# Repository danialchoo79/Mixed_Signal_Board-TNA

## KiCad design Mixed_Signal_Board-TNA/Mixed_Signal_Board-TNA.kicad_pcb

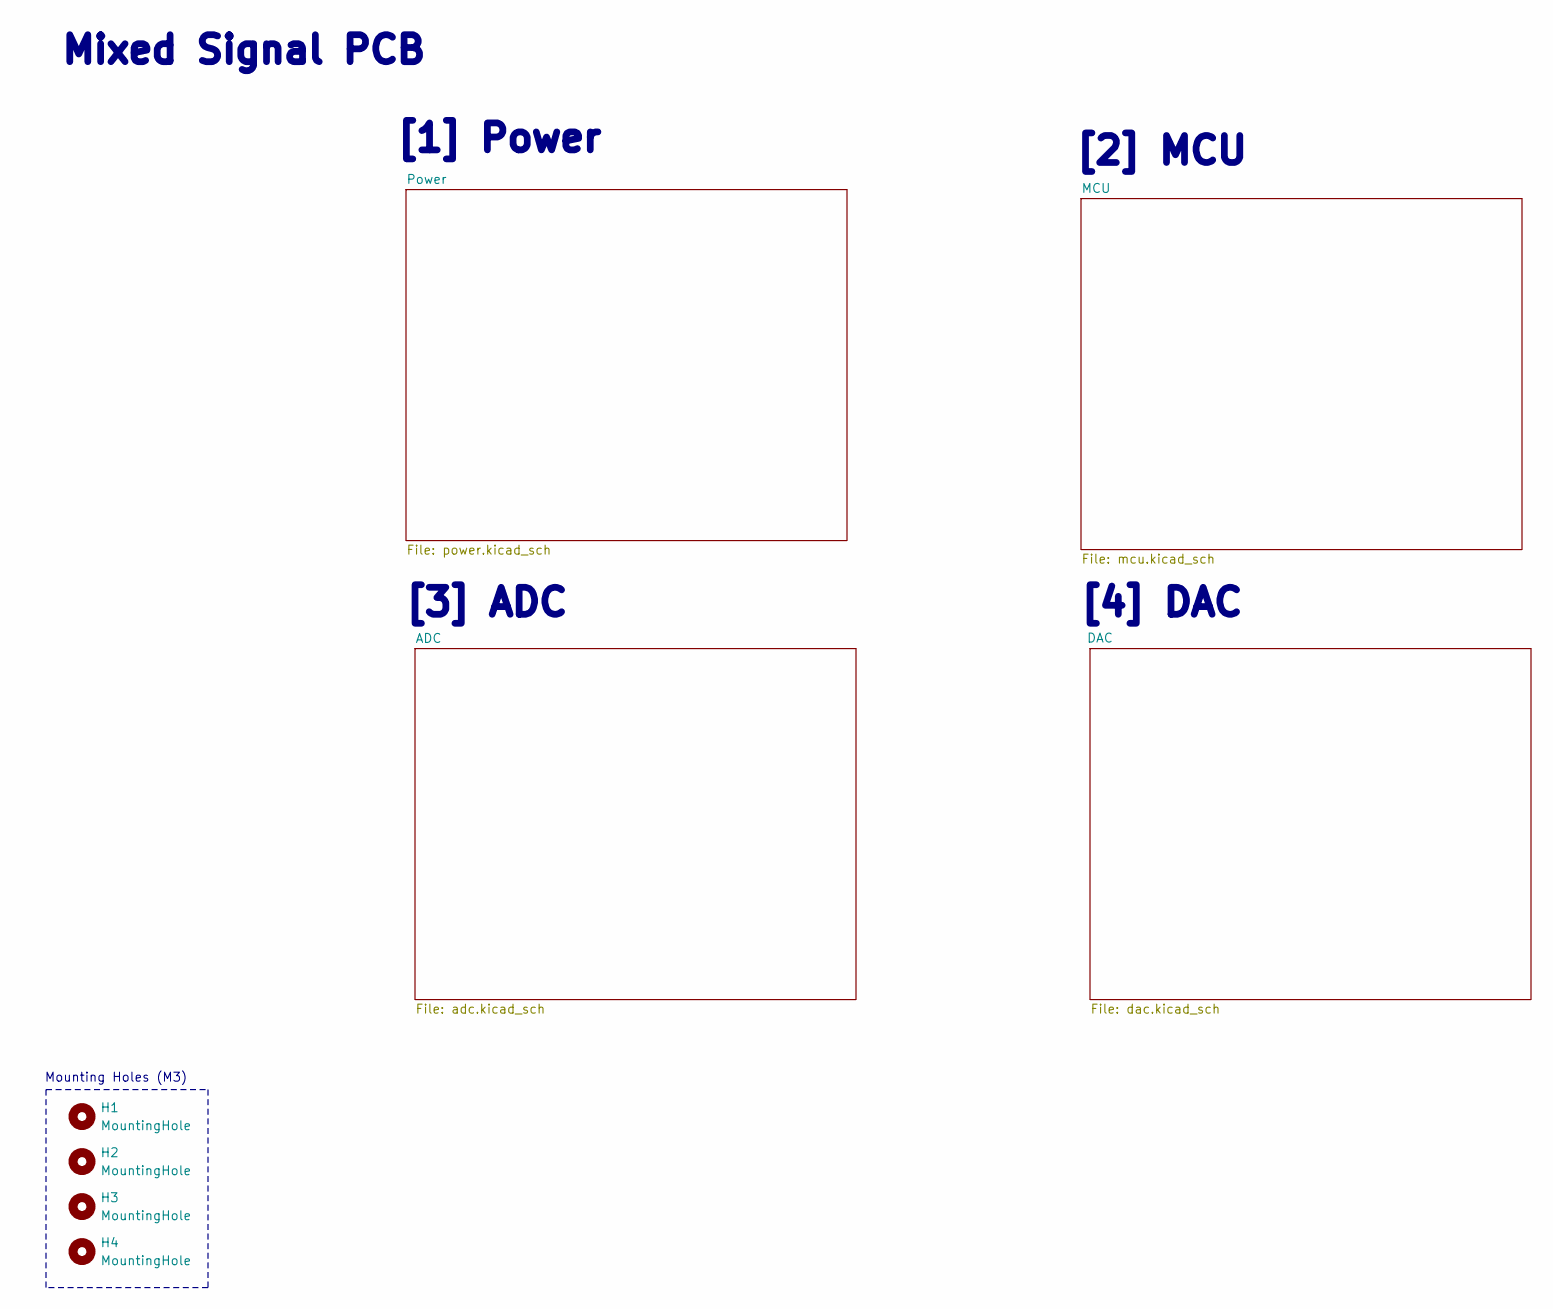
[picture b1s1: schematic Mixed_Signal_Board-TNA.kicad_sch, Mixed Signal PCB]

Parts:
H1, H2, H3, H4: MountingHole; MountingHole_3.2mm_M3

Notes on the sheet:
[2] MCU
[4] DAC
Mounting Holes (M3)
[3] ADC
Mixed Signal PCB
[1] Power

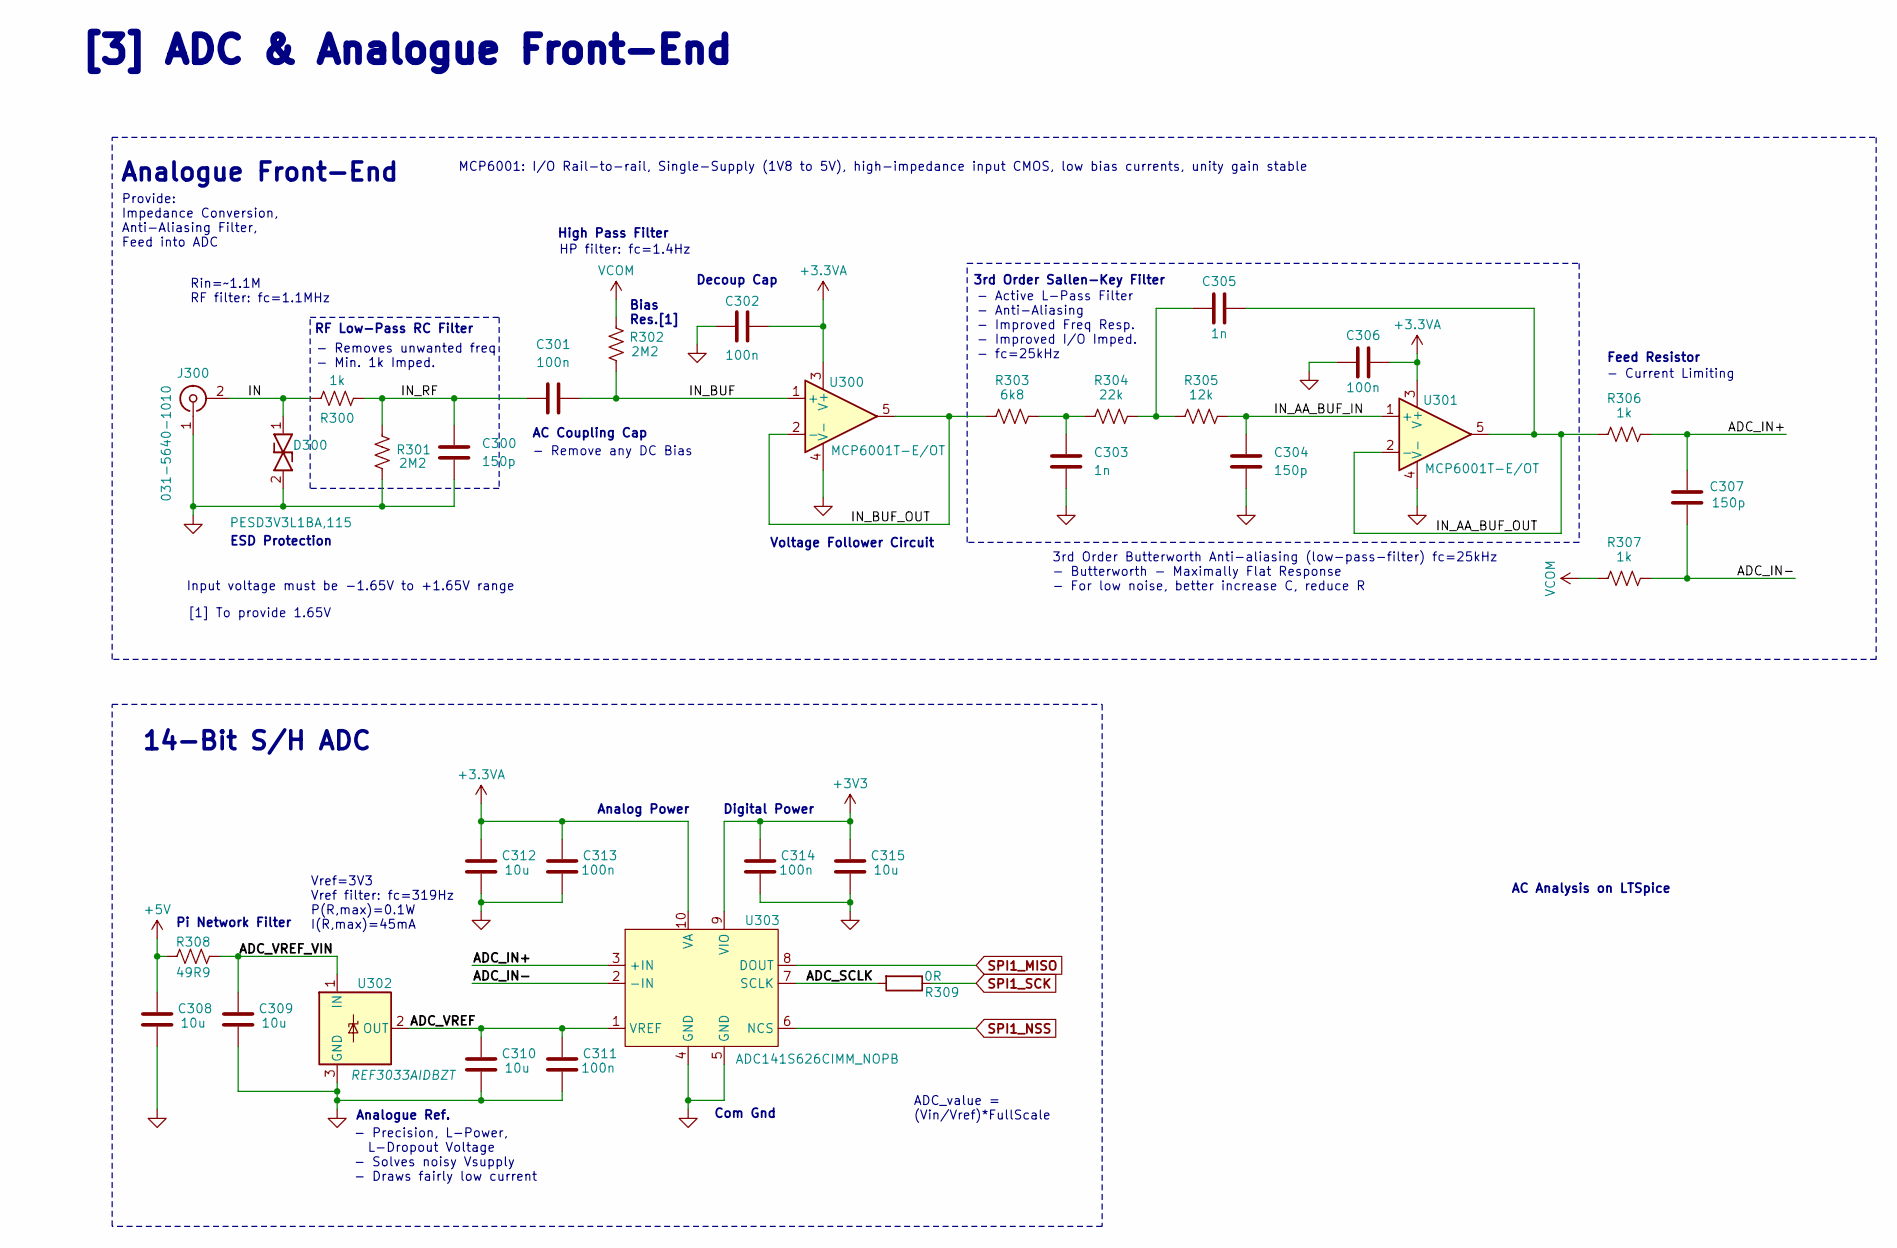
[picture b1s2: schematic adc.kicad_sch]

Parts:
C300, C304, C307: 150p; C_0402_1005Metric
C301, C302, C306, C311, C313, C314: 100n; C_0402_1005Metric
C303, C305: 1n; C_0402_1005Metric
C308, C309: 10u; C_0402_1005Metric
C310, C312, C315: 10u; C_0603_1608Metric
D300: PESD3V3L1BA,115; SOD2512X110N; Mouser Part Number 771-PESD3V3L1BA-T/R
J300: 031-5640-1010; 03156401010
R300, R306, R307: 1k; R_0402_1005Metric
R301, R302: 2M2; R_0603_1608Metric
R303: 6k8; R_0402_1005Metric
R304: 22k; R_0402_1005Metric
R305: 12k; R_0402_1005Metric
R308: 49R9; R_0402_1005Metric
R309: 0R; R_0402_1005Metric
U300, U301: MCP6001T-E/OT; SOT95P270X145-5N
U302: REF3033AIDBZT; SOT-23
U303: ADC141S626CIMM_NOPB; SOP50P490X110-10N

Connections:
+3.3VA: C302.1, C306.2, C312.1, C313.1, U300.3 (V+), U301.3 (V+), U303.10 (VA); also elsewhere on the board
+5V: C308.1, R308.2; also elsewhere on the board
/ADC/ADC_IN+: C307.1, R306.1, U303.3 (+IN)
/ADC/ADC_IN-: C307.2, R307.1, U303.2 (-IN)
/ADC/ADC_SCLK: R309.2, U303.7 (SCLK)
/ADC/ADC_VREF: C310.1, C311.1, U302.2 (OUT), U303.1 (VREF)
/ADC/ADC_VREF_VIN: C309.1, R308.1, U302.1 (IN)
/ADC/IN: D300.1 (K1), J300.2 (Ext), R300.2
/ADC/IN_AA_BUF_IN: C304.1, R305.1, U301.1 (+)
/ADC/IN_AA_BUF_OUT: C305.2, R306.2, U301.2 (-), U301.5
/ADC/IN_BUF: C301.1, R302.1, U300.1 (+)
/ADC/IN_BUF_OUT: R303.2, U300.2 (-), U300.5
/ADC/IN_RF: C300.1, C301.2, R300.1, R301.2
unnamed: C303.1, R303.1, R304.2
unnamed: C305.1, R304.1, R305.2
SPI1_MISO: U303.8 (DOUT); also elsewhere on the board
SPI1_NSS: U303.6 (NCS); also elsewhere on the board
SPI1_SCK: R309.1; also elsewhere on the board
VCOM: R302.2, R307.2; also elsewhere on the board
VREF_DAC: C300.2, C302.2, C303.2, C304.2, C306.1, C308.2, C309.2, C310.2, C311.2, C312.2, C313.2, C314.2, C315.2, D300.2 (K2), J300.1 (In), R301.1, U300.4 (V-), U301.4 (V-), U302.3 (GND), U303.4 (GND), U303.5 (GND); also elsewhere on the board

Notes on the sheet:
3rd Order Sallen-Key Filter
Decoup Cap
- Precision, L-Power, L-Dropout Voltage - Solves noisy Vsupply - Draws fairly low current
MCP6001: I/O Rail-to-rail, Single-Supply (1V8 to 5V), high-impedance input CMOS, low bias currents, unity gain stable
Pi Network Filter
ADC_value = (Vin/Vref)*FullScale
Voltage Follower Circuit
- Active L-Pass Filter - Anti-Aliasing - Improved Freq Resp. - Improved I/O Imped. - fc=25kHz
Analogue Ref.
RF Low-Pass RC Filter
[3] ADC & Analogue Front-End
HP filter: fc=1.4Hz
Feed Resistor
Com Gnd
High Pass Filter
Digital Power
Analogue Front-End
Analog Power
Bias Res.[1]
AC Coupling Cap
14-Bit S/H ADC
3rd Order Butterworth Anti-aliasing (low-pass-filter) fc=25kHz - Butterworth - Maximally Flat Response - For low noise, better increase C, reduce R
Provide: Impedance Conversion, Anti-Aliasing Filter, Feed into ADC
ESD Protection
AC Analysis on LTSpice
- Current Limiting
Input voltage must be -1.65V to +1.65V range
Rin=~1.1M RF filter: fc=1.1MHz
- Remove any DC Bias
Vref=3V3 Vref filter: fc=319Hz P(R,max)=0.1W I(R,max)=45mA
- Removes unwanted freq - Min. 1k Imped.
[1] To provide 1.65V

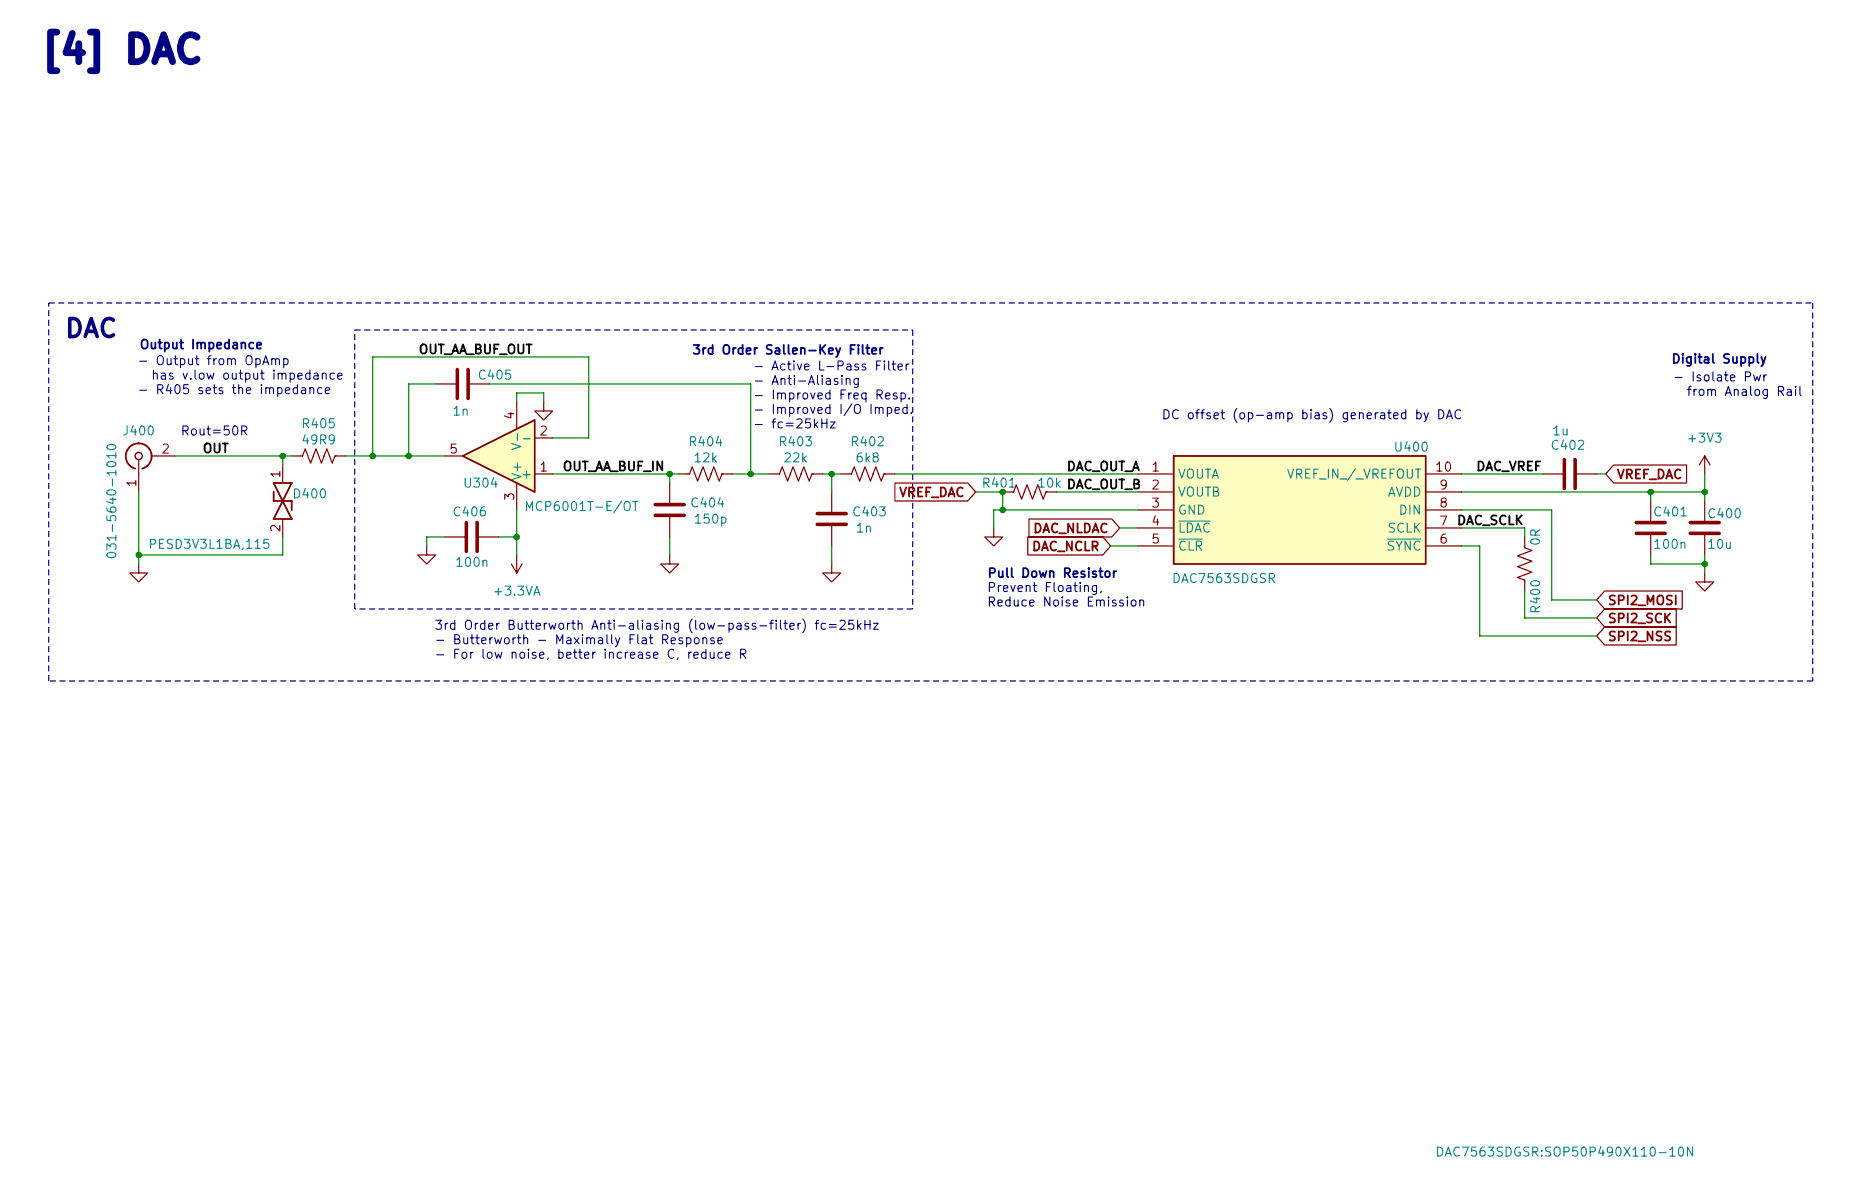
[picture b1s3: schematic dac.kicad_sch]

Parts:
C400: 10u; C_0603_1608Metric
C401, C406: 100n; C_0402_1005Metric
C402: 1u; C_0402_1005Metric
C403, C405: 1n; C_0402_1005Metric
C404: 150p; C_0402_1005Metric
D400: PESD3V3L1BA,115; SOD2512X110N; Mouser Part Number 771-PESD3V3L1BA-T/R
J400: 031-5640-1010; 03156401010
R400: 0R; R_0402_1005Metric
R401: 10k; R_0402_1005Metric
R402: 6k8; R_0402_1005Metric
R403: 22k; R_0402_1005Metric
R404: 12k; R_0402_1005Metric
R405: 49R9; R_0402_1005Metric
U304: MCP6001T-E/OT; SOT95P270X145-5N
U400: DAC7563SDGSR; SOP50P490X110-10N; Mouser Part Number 595-DAC7563SDGSR

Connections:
+3.3VA: C406.2, U304.3 (V+); also elsewhere on the board
/DAC/DAC_OUT_A: R402.1, U400.1 (VOUTA)
/DAC/DAC_OUT_B: R401.2, U400.2 (VOUTB)
/DAC/DAC_SCLK: R400.2, U400.7 (SCLK)
/DAC/DAC_VREF: C402.2, U400.10 (VREF_IN_/_VREFOUT)
/DAC/OUT: D400.1 (K1), J400.2 (Ext), R405.2
/DAC/OUT_AA_BUF_IN: C404.1, R404.2, U304.1 (+)
/DAC/OUT_AA_BUF_OUT: C405.1, R405.1, U304.2 (-), U304.5
DAC_NCLR: U400.5 (~CLR); also elsewhere on the board
DAC_NLDAC: U400.4 (~LDAC); also elsewhere on the board
unnamed: C403.1, R402.2, R403.1
unnamed: C405.2, R403.2, R404.1
SPI2_MOSI: U400.8 (DIN); also elsewhere on the board
SPI2_NSS: U400.6 (~SYNC); also elsewhere on the board
SPI2_SCK: R400.1; also elsewhere on the board
VREF_DAC: C400.2, C401.2, C402.1, C403.2, C404.2, C406.1, D400.2 (K2), J400.1 (In), R401.1, U304.4 (V-), U400.3 (GND); also elsewhere on the board

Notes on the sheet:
Rout=50R
[4] DAC
- Active L-Pass Filter - Anti-Aliasing - Improved Freq Resp. - Improved I/O Imped. - fc=25kHz
DAC
3rd Order Butterworth Anti-aliasing (low-pass-filter) fc=25kHz - Butterworth - Maximally Flat Response - For low noise, better increase C, reduce R
Pull Down Resistor
Output Impedance
Digital Supply
3rd Order Sallen-Key Filter
DC offset (op-amp bias) generated by DAC
Prevent Floating, Reduce Noise Emission
- Output from OpAmp has v.low output impedance - R405 sets the impedance
- Isolate Pwr from Analog Rail

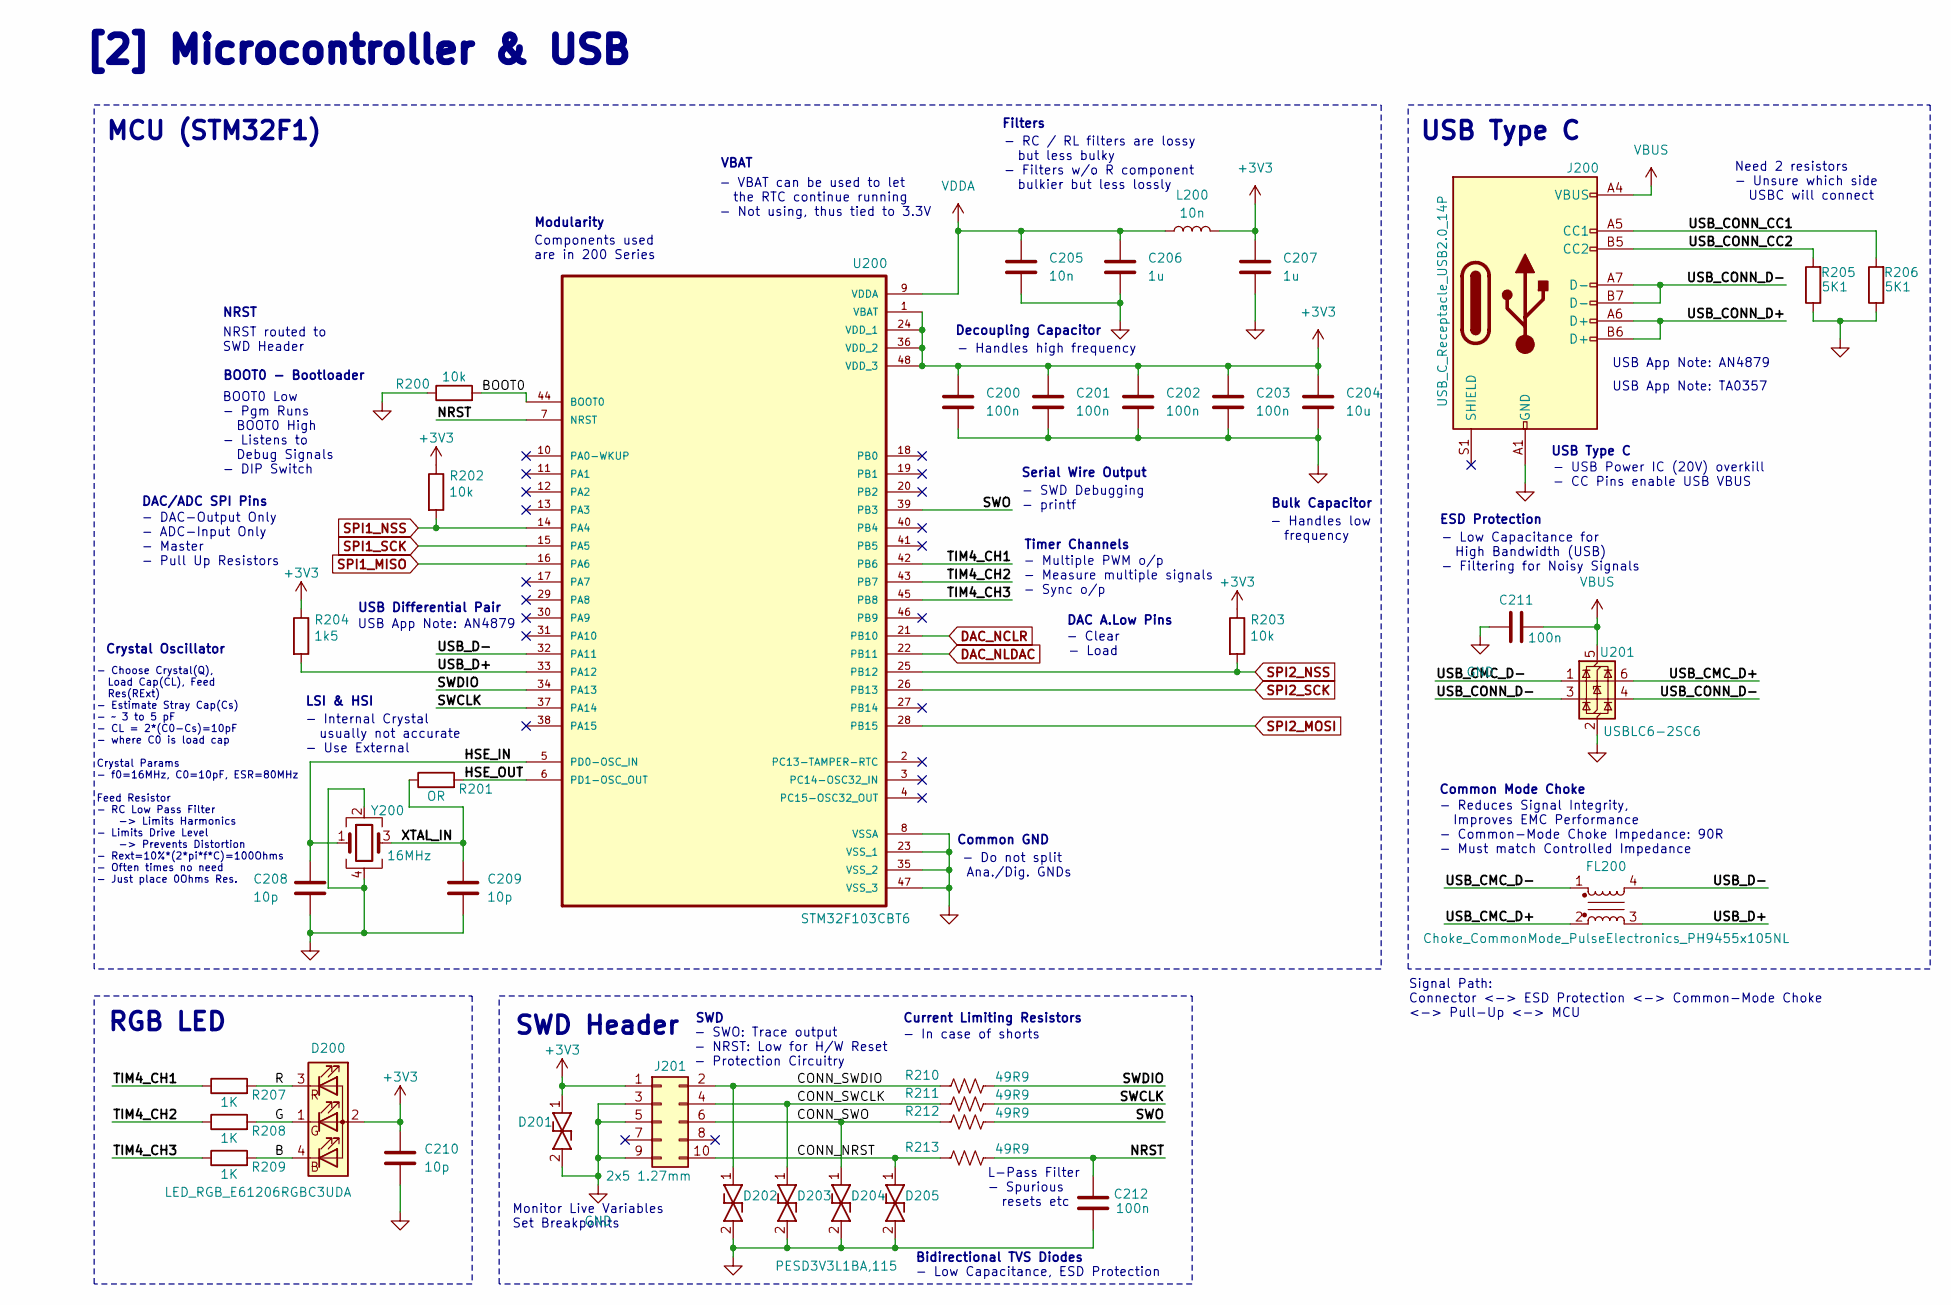
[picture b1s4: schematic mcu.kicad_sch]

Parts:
C200, C201, C202, C203, C211, C212: 100n; C_0402_1005Metric
C204: 10u; C_0603_1608Metric
C205: 10n; C_0402_1005Metric
C206, C207: 1u; C_0603_1608Metric
C208, C209, C210: 10p; C_0402_1005Metric
D200: LED_RGB_E61206RGBC3UDA; LED_Avago_PLCC4_3.2x2.8mm_CW
D201, D202, D203, D204, D205: PESD3V3L1BA,115; SOD2512X110N; Mouser Part Number 771-PESD3V3L1BA-T/R
FL200: Choke_CommonMode_PulseElectronics_PH9455x105NL; CMF3216F-900-2P-T
J200: USB_C_Receptacle_USB2.0_14P; USB_C_Receptacle_JAE_DX07S016JA1R1500
J201: 2x5 1.27mm; PinHeader_2x05_P1.27mm_Vertical_SMD
L200: 10n; L_0402_1005Metric
R200, R202, R203: 10k; R_0402_1005Metric
R201: OR; R_0402_1005Metric
R204: 1k5; R_0402_1005Metric
R205, R206: 5K1; R_0402_1005Metric
R207, R208, R209: 1K; R_0402_1005Metric
R210, R211, R212, R213: 49R9; R_0402_1005Metric
U200: STM32F103CBT6; QFP50P900X900X160-48N; PARTREV 10
U201: USBLC6-2SC6; SOT-23-6
Y200: 16MHz; Crystal_SMD_3225-4Pin_3.2x2.5mm

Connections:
/MCU/B: D200.4 (BK), R209.2
/MCU/BOOT0: R200.2, U200.44 (BOOT0)
/MCU/CONN_NRST: D205.1 (K1), J201.10, R213.2
/MCU/CONN_SWCLK: D203.1 (K1), J201.4, R211.2
/MCU/CONN_SWDIO: D202.1 (K1), J201.2, R210.2
/MCU/CONN_SWO: D204.1 (K1), J201.6, R212.2
/MCU/G: D200.1 (GK), R208.2
/MCU/HSE_IN: C208.1, U200.5 (PD0-OSC_IN), Y200.1
/MCU/HSE_OUT: R201.2, U200.6 (PD1-OSC_OUT)
/MCU/NRST: C212.2, R213.1, U200.7 (NRST)
/MCU/R: D200.3 (RK), R207.2
/MCU/SWCLK: R211.1, U200.37 (PA14)
/MCU/SWDIO: R210.1, U200.34 (PA13)
/MCU/SWO: R212.1, U200.39 (PB3)
/MCU/TIM4_CH1: R207.1, U200.42 (PB6)
/MCU/TIM4_CH2: R208.1, U200.43 (PB7)
/MCU/TIM4_CH3: R209.1, U200.45 (PB8)
/MCU/USB_CMC_D+: FL200.2, U201.6 (I/O1)
/MCU/USB_CMC_D-: FL200.1, U201.1 (I/O1)
/MCU/USB_CONN_CC1: J200.A5 (CC1), R206.2
/MCU/USB_CONN_CC2: J200.B5 (CC2), R205.2
/MCU/USB_D+: FL200.3, R204.2, U200.33 (PA12)
/MCU/USB_D-: FL200.4, U200.32 (PA11)
/MCU/XTAL_IN: C209.1, R201.1, Y200.3
DAC_NCLR: U200.21 (PB10); also elsewhere on the board
DAC_NLDAC: U200.22 (PB11); also elsewhere on the board
SPI1_MISO: U200.16 (PA6); also elsewhere on the board
SPI1_NSS: R202.2, U200.14 (PA4); also elsewhere on the board
SPI1_SCK: U200.15 (PA5); also elsewhere on the board
SPI2_MOSI: U200.28 (PB15); also elsewhere on the board
SPI2_NSS: R203.2, U200.25 (PB12); also elsewhere on the board
SPI2_SCK: U200.26 (PB13); also elsewhere on the board
VBUS: C211.2, J200.A4 (VBUS), J200.A9 (VBUS), J200.B4 (VBUS), J200.B9 (VBUS), U201.5 (VBUS); also elsewhere on the board
VDDA: C205.1, C206.1, L200.1, U200.9 (VDDA)
VREF_DAC: C200.2, C201.2, C202.2, C203.2, C204.2, C205.2, C206.2, C207.2, C208.2, C209.2, C210.2, C211.1, C212.1, D201.2 (K2), D202.2 (K2), D203.2 (K2), D204.2 (K2), D205.2 (K2), J200.A1 (GND), J200.A12 (GND), J200.B1 (GND), J200.B12 (GND), J201.3, J201.5, J201.9, R200.1, R205.1, R206.1, U200.8 (VSSA), U200.23 (VSS_1), U200.35 (VSS_2), U200.47 (VSS_3), U201.2 (GND), Y200.2, Y200.4; also elsewhere on the board

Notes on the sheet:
Monitor Live Variables Set Breakpoints
BOOT0 - Bootloader
Common Mode Choke
RGB LED
VBAT
USB Type C
- USB Power IC (20V) overkill - CC Pins enable USB VBUS
- Low Capacitance, ESD Protection
Current Limiting Resistors
Bidirectional TVS Diodes
NRST
MCU (STM32F1)
- Do not split Ana./Dig. GNDs
- Choose Crystal(Q), Load Cap(CL), Feed Res(RExt) - Estimate Stray Cap(Cs) - ~ 3 to 5 pF - CL = 2*(C0-Cs)=10pF - where C0 is load cap Crystal Params - f0=16MHz, C0=10pF, ESR=80MHz Feed Resistor - RC Low Pass Filter -> Limits Harmonics - Limits Drive Level -> Prevents Distortion - Rext=10%*(2*pi*f*C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
USB Differential Pair
- Internal Crystal usually not accurate - Use External
- Clear - Load
ESD Protection
Decoupling Capacitor
NRST routed to SWD Header
[2] Microcontroller & USB
SWD
LSI & HSI
BOOT0 Low - Pgm Runs BOOT0 High - Listens to Debug Signals - DIP Switch
Filters
Signal Path: Connector <-> ESD Protection <-> Common-Mode Choke <-> Pull-Up <-> MCU
L-Pass Filter - Spurious resets etc
- Reduces Signal Integrity, Improves EMC Performance - Common-Mode Choke Impedance: 90R - Must match Controlled Impedance
DAC A.Low Pins
Crystal Oscillator
USB App Note: AN4879
Modularity
- Multiple PWM o/p - Measure multiple signals - Sync o/p
- Low Capacitance for High Bandwidth (USB) - Filtering for Noisy Signals
- RC / RL filters are lossy but less bulky - Filters w/o R component bulkier but less lossly
USB App Note: TA0357
SWD Header
DAC/ADC SPI Pins
- SWO: Trace output - NRST: Low for H/W Reset - Protection Circuitry
Components used are in 200 Series

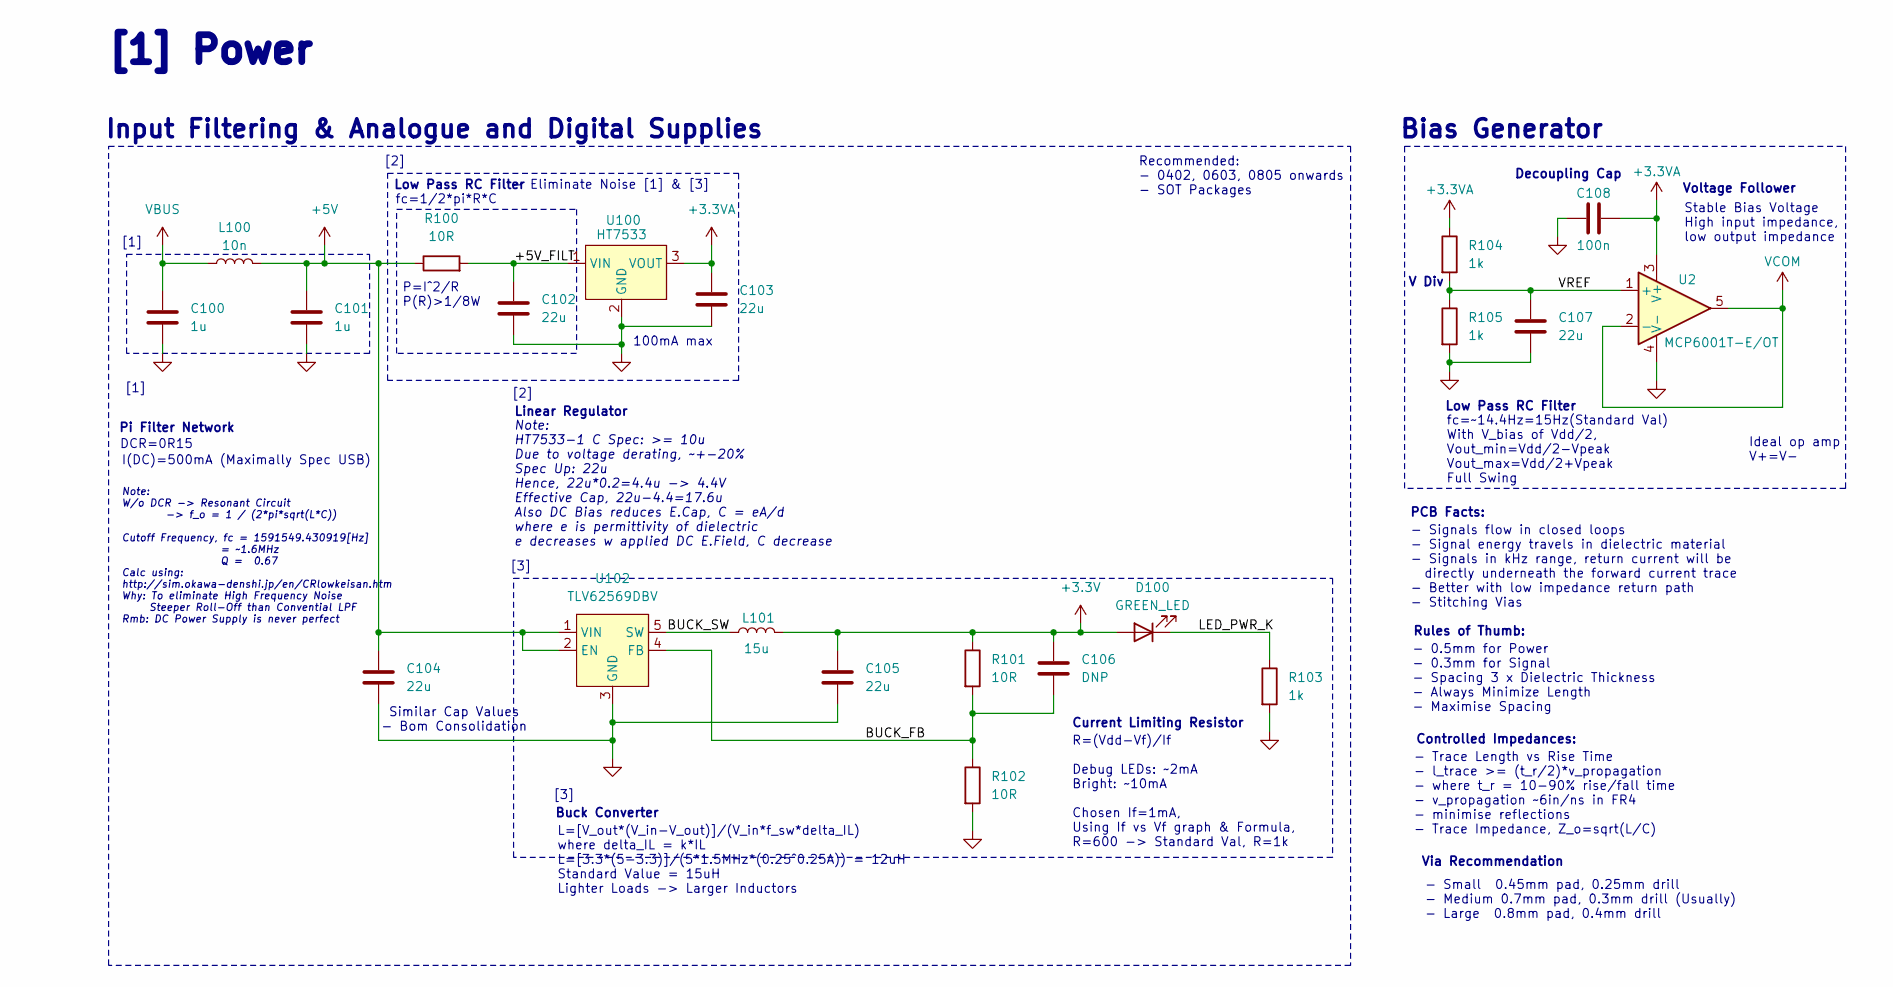
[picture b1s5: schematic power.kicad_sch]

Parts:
C100, C101: 1u; C_0603_1608Metric
C102, C103, C104, C105, C107: 22u; C_0805_2012Metric
C106: DNP; C_0402_1005Metric
C108: 100n; C_0402_1005Metric
D100: GREEN_LED; LED_0603_1608Metric
L100: 10n; L_0402_1005Metric
L101: 15u; L_Sunlord_MWSA0603S
R100: 10R; R_0805_2012Metric
R101, R102: 10R; R_0402_1005Metric
R103, R104, R105: 1k; R_0402_1005Metric
U1: (no value)
U2: MCP6001T-E/OT; SOT95P270X145-5N
U100: HT7533; SOT89
U102: TLV62569DBV; SOT95P280X145-5N

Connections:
+3.3VA: C103.1, C108.2, R104.1, U2.3 (V+), U100.3 (VOUT); also elsewhere on the board
+5V: C101.1, C104.1, L100.2, R100.1, U102.1 (VIN), U102.2 (EN); also elsewhere on the board
/Power/+5V_FILT: C102.1, R100.2, U100.1 (VIN)
/Power/BUCK_FB: C106.2, R101.2, R102.1, U102.4 (FB)
/Power/BUCK_SW: L101.1, U102.5 (SW)
/Power/LED_PWR_K: D100.1 (K), R103.1
/Power/VREF: C107.1, R104.2, R105.1, U2.1 (+)
VBUS: C100.1, L100.1; also elsewhere on the board
VCOM: U2.2 (-), U2.5; also elsewhere on the board
VREF_DAC: C100.2, C101.2, C102.2, C103.2, C104.2, C105.2, C107.2, C108.1, R102.2, R103.2, R105.2, U2.4 (V-), U100.2 (GND), U102.3 (GND); also elsewhere on the board

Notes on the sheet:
Linear Regulator
[2]
Rules of Thumb:
P=I^2/R P(R)>1/8W
- Small 0.45mm pad, 0.25mm drill - Medium 0.7mm pad, 0.3mm drill (Usually) - Large 0.8mm pad, 0.4mm drill
Note: HT7533-1 C Spec: >= 10u Due to voltage derating, ~+-20% Spec Up: 22u Hence, 22u*0.2=4.4u -> 4.4V Effective Cap, 22u-4.4=17.6u Also DC Bias reduces E.Cap, C = eA/d where e is permittivity of dielectric e decreases w applied DC E.Field, C decrease
Ideal op amp V+=V-
R=(Vdd-Vf)/If Debug LEDs: ~2mA Bright: ~10mA Chosen If=1mA, Using If vs Vf graph & Formula, R=600 -> Standard Val, R=1k
Similar Cap Values - Bom Consolidation
Low Pass RC Filter
- Signals flow in closed loops - Signal energy travels in dielectric material - Signals in kHz range, return current will be directly underneath the forward current trace - Better with low impedance return path - Stitching Vias
[3]
fc=~14.4Hz=15Hz(Standard Val) With V_bias of Vdd/2, Vout_min=Vdd/2-Vpeak Vout_max=Vdd/2+Vpeak Full Swing
Note: W/o DCR -> Resonant Circuit -> f_o = 1 / (2*pi*sqrt(L*C)) Cutoff Frequency, fc = 1591549.430919[Hz] = ~1.6MHz Q = 0.67 Calc using: http://sim.okawa-denshi.jp/en/CRlowkeisan.htm Why: To eliminate High Frequency Noise Steeper Roll-Off than Convential LPF Rmb: DC Power Supply is never perfect
[1]
Stable Bias Voltage High input impedance, low output impedance
V Div
Via Recommendation
Recommended: - 0402, 0603, 0805 onwards - SOT Packages
- Trace Length vs Rise Time - l_trace >= (t_r/2)*v_propagation - where t_r = 10-90% rise/fall time - v_propagation ~6in/ns in FR4 - minimise reflections - Trace Impedance, Z_o=sqrt(L/C)
100mA max
Pi Filter Network
Current Limiting Resistor
Buck Converter
Voltage Follower
L=[V_out*(V_in-V_out)]/(V_in*f_sw*delta_IL) where delta_IL = k*IL L=[3.3*(5-3.3)]/(5*1.5MHz*(0.25^0.25A)) = 12uH Standard Value = 15uH Lighter Loads -> Larger Inductors
I(DC)=500mA (Maximally Spec USB)
- 0.5mm for Power - 0.3mm for Signal - Spacing 3 x Dielectric Thickness - Always Minimize Length - Maximise Spacing
Decoupling Cap
Bias Generator
PCB Facts:
DCR=0R15
- Eliminate Noise [1] & [3] fc=1/2*pi*R*C
Controlled Impedances:
[1] Power
Input Filtering & Analogue and Digital Supplies

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
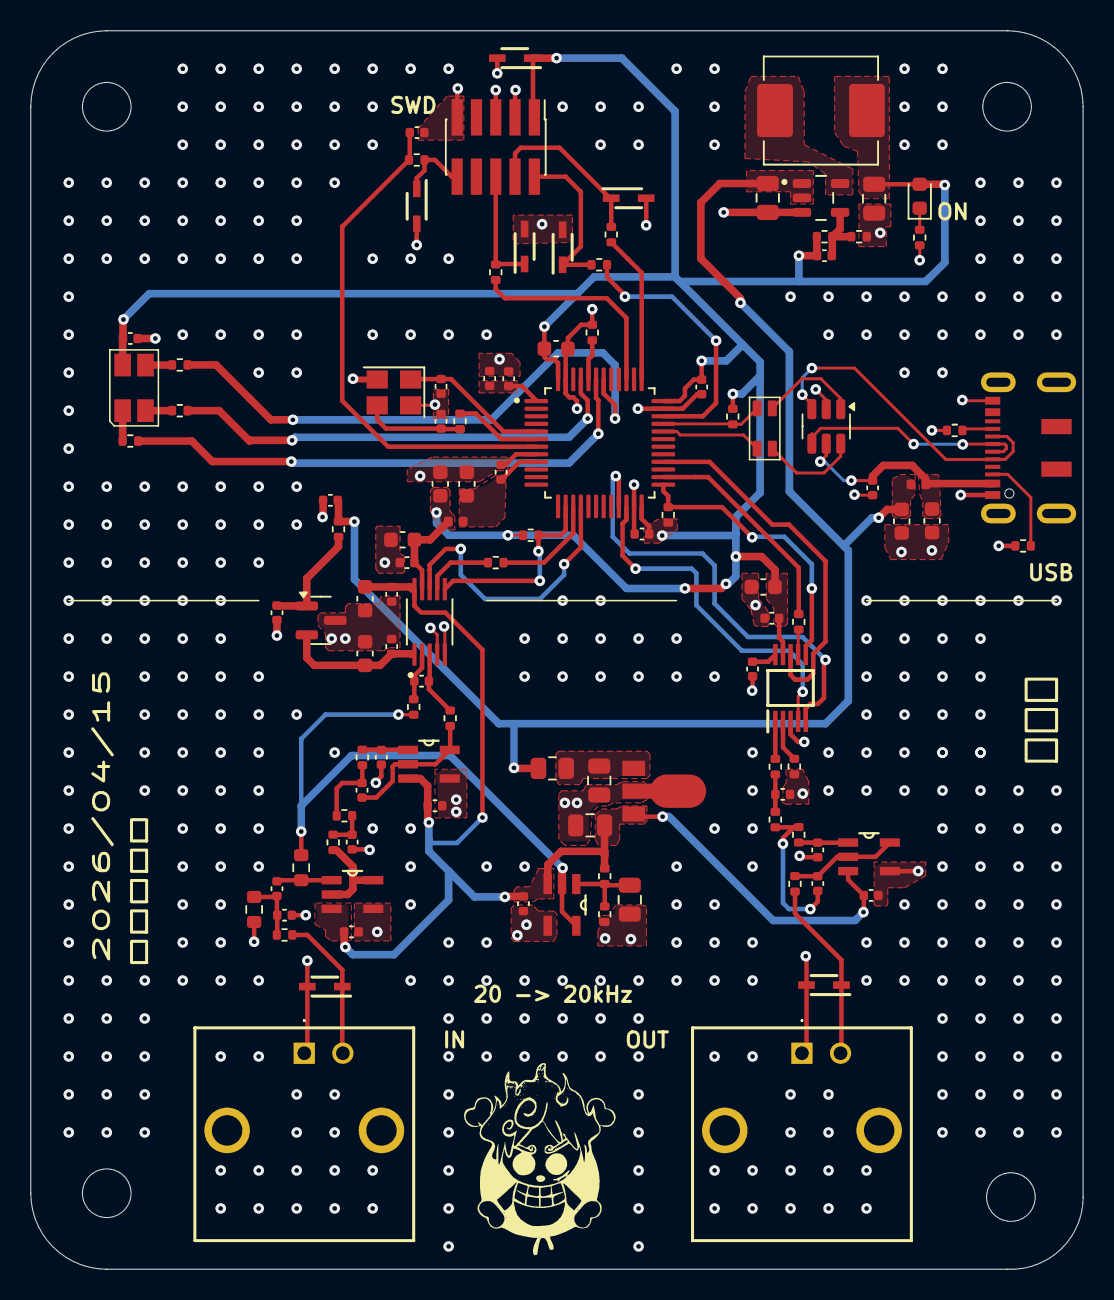
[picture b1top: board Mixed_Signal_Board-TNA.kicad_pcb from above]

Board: 4 copper layers, 69.3 x 81.5 mm, 114 parts (0 on the bottom side), 68 nets.

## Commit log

2026-04-01 Just Before Layout
2026-04-02 Done Layout
2026-04-15 Routed but differential pair not right
